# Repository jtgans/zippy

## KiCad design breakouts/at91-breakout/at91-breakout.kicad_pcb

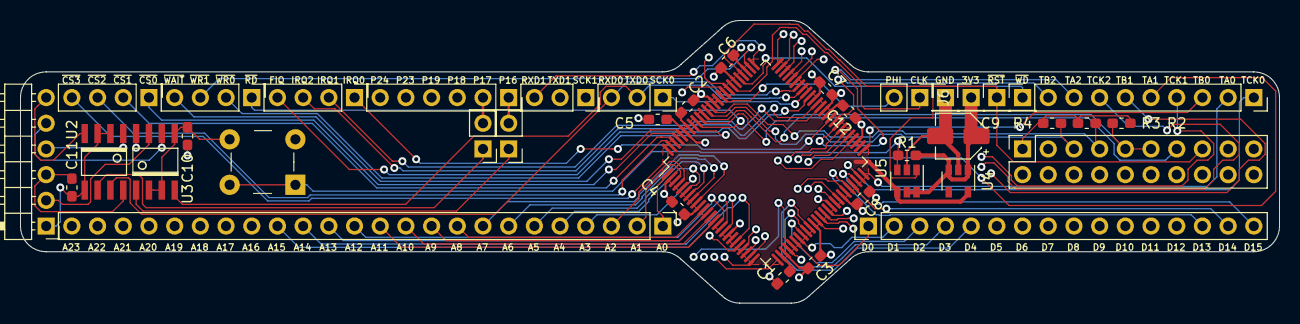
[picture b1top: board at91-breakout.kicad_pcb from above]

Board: 4 copper layers, 124.5 x 27.9 mm, 40 parts (0 on the bottom side), 93 nets.

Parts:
C1, C2, C3, C4, C5, C6, C7, C8, C10, C11, C12: 10nF; C_0603_1608Metric_Pad1.05x0.95mm_HandSolder
C9: 1uF; CP_Elec_4x4.5
J1: UART0; PinSocket_1x03_P2.54mm_Vertical
J2: TIMER; PinSocket_1x09_P2.54mm_Vertical
J3: ADDR[0..23]; PinHeader_1x24_P2.54mm_Vertical
J4: ~WDOVF; PinHeader_1x01_P2.54mm_Vertical
J5: GPIO; PinSocket_1x06_P2.54mm_Vertical
J6: CLKINOUT; PinHeader_1x02_P2.54mm_Vertical
J7: ~RESET; PinHeader_1x01_P2.54mm_Vertical
J8: DATA[0..15]; PinHeader_1x16_P2.54mm_Vertical
J9: ~CS[0..3]; PinHeader_1x04_P2.54mm_Vertical
J10: BUSCTL; PinHeader_1x04_P2.54mm_Vertical
J12: RTSCB0; PinHeader_1x02_P2.54mm_Vertical
J14: IRQ; PinHeader_1x04_P2.54mm_Vertical
J15: JTAG; PinSocket_2x10_P2.54mm_Vertical
J16: CTSCB0; PinHeader_1x02_P2.54mm_Vertical
J18: UART1; PinSocket_1x03_P2.54mm_Vertical
J19: VDD; PinHeader_1x01_P2.54mm_Vertical
J21: GND; PinHeader_1x01_P2.54mm_Vertical
J22: TTY; PinHeader_1x06_P2.54mm_Horizontal
R1, R2, R3, R4: 100K; R_0603_1608Metric_Pad1.05x0.95mm_HandSolder
S1: B3F-1000; Switch_Tactile_THT_B3F-1xxx
U1: AT91R40008; LQFP-100_14x14mm_P0.5mm
U2: BB Powered; SO-8
U3: PC Powered; SO-8
U4: MIC5504-1.8YM5; SOT-23-5
U5: MAX6355TW; SOT-23-6

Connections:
+1V8: C1.2, C2.2, C12.2, U1.27, U1.61, U1.94, U4.5, U5.4
+3V3: C3.2, C4.2, C5.2, C6.2, C7.2, C8.2, C9.1, C10.1, J15.1, J15.2, J19.1, R1.1, R2.1, R3.1, R4.1, U1.10, U1.28, U1.44, U1.62, U1.81, U1.95, U2.8, U4.1, U4.3, U5.5, U5.6
/ADDR0: J3.1, U1.1
/ADDR1: J3.2, U1.3
/ADDR2: J3.3, U1.4
/ADDR3: J3.4, U1.5
/ADDR4: J3.5, U1.6
/ADDR5: J3.6, U1.7
/ADDR6: J3.7, U1.8
/ADDR7: J3.8, U1.9
/ADDR8: J3.9, U1.11
/ADDR9: J3.10, U1.12
/ADDR10: J3.11, U1.13
/ADDR11: J3.12, U1.14
/ADDR12: J3.13, U1.15
/ADDR13: J3.14, U1.16
/ADDR14: J3.15, U1.17
/ADDR15: J3.16, U1.20
/ADDR16: J3.17, U1.21
/ADDR17: J3.18, U1.22
/ADDR18: J3.19, U1.23
/ADDR19: J3.20, U1.24
/ADDR20: J3.21, U1.25
/ADDR21: J3.22, U1.26
/ADDR22: J3.23, U1.29
/ADDR23: J3.24, U1.30
/DATA0: J8.1, U1.31
/DATA1: J8.2, U1.32
/DATA2: J8.3, U1.33
/DATA3: J8.4, U1.34
/DATA4: J8.5, U1.35
/DATA5: J8.6, U1.37
/DATA6: J8.7, U1.38
/DATA7: J8.8, U1.39
/DATA8: J8.9, U1.40
/DATA9: J8.10, U1.41
/DATA10: J8.11, U1.42
/DATA11: J8.12, U1.43
/DATA12: J8.13, U1.45
/DATA13: J8.14, U1.46
/DATA14: J8.15, U1.47
/DATA15: J8.16, U1.48
/FIQ: J14.4, U1.66
/FTDI_GND: C11.2, J22.1, U3.2, U3.3, U3.5
/FTDI_RX: J22.5, U2.6
/FTDI_TX: J22.4, U3.1
/FTDI_VCC: C11.1, J22.3, U3.8
/IRQ0: J14.1, U1.60
/IRQ1: J14.2, U1.63
/IRQ2: J14.3, U1.64
/MCKI: J6.1, U1.82
/MCKO: J6.2, U1.85
/P16: J5.1, J12.2, U1.70
/P17: J5.2, J16.2, U1.71
/P18: J5.3, U1.72
/P19: J5.4, U1.73
/P23: J5.5, U1.83
/P24: J5.6, U1.84
/RXD0: J1.3, U1.69, U3.7
/RXD1: J18.3, U1.76
/SCK0: J1.1, U1.67
/SCK1: J18.1, U1.74
/TCK: J15.9, J15.11, R2.2, U1.91
/TCLK0: J2.1, U1.49
/TCLK1: J2.4, U1.54
/TCLK2: J2.7, U1.57
/TDI: J15.5, R4.2, U1.89
/TDO: J15.13, U1.90
/TIOA0: J2.2, U1.50
/TIOA1: J2.5, U1.55
/TIOA2: J2.8, U1.58
/TIOB0: J2.3, U1.51
/TIOB1: J2.6, U1.56
/TIOB2: J2.9, U1.59
/TMS: J15.7, R3.2, U1.88
/TXD0: J1.2, U1.68, U2.4
/TXD1: J18.2, U1.75
/~CS0: J9.1, U1.97
/~CS1: J9.2, U1.98
/~CS2: J9.3, U1.99
/~CS3: J9.4, U1.100
/~CTS0: J16.1, U3.6
/~FTDI_CTS: J22.2, U2.7
/~FTDI_RTS: J22.6, U3.4
/~MR: R1.2, S1.1, S1.2, U5.3
/~RD: J10.1, U1.92
/~RESET: J7.1, J15.15, U1.79, U5.1
/~RTS0: J12.1, U2.1
/~WAIT: J10.4, U1.96
/~WDOVF: J4.1, U1.80
/~WR0: J10.2, U1.93
/~WR1: J10.3, U1.77
GND: C1.1, C2.1, C3.1, C4.1, C5.1, C6.1, C7.1, C8.1, C9.2, C10.2, C12.1, J15.4, J15.6, J15.8, J15.10, J15.12, J15.14, J15.16, J15.18, J15.20, J21.1, S1.3, S1.4, U1.2, U1.18, U1.19, U1.36, U1.52, U1.53, U1.65, U1.78, U1.86, U1.87, U2.2, U2.3, U2.5, U4.2, U5.2

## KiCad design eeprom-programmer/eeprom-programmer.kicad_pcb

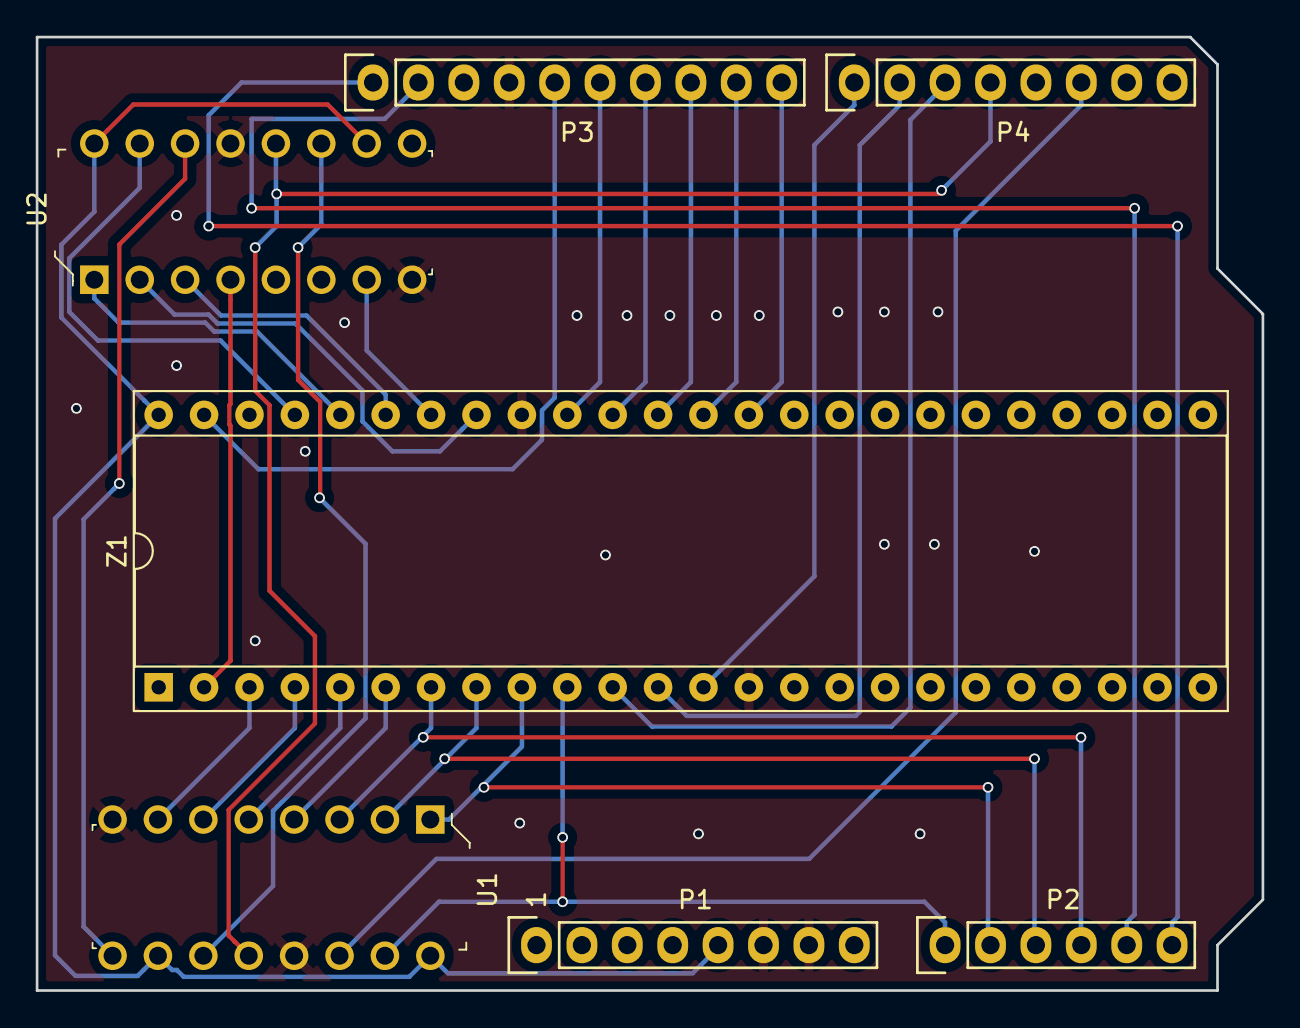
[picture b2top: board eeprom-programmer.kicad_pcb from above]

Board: 2 copper layers, 68.6 x 53.3 mm, 7 parts (0 on the bottom side), 31 nets.

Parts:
P1: Power; Socket_Strip_Arduino_1x08
P2: Analog; Socket_Strip_Arduino_1x06
P3: Digital; Socket_Strip_Arduino_1x10
P4: Digital; Socket_Strip_Arduino_1x08
U1, U2: SN74HC595N; DIP-16_W7.62mm
Z1: 48-6554-11; DIP-48_W15.24mm_Socket

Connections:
+5V: P1.5, U1.10, U1.16, U2.10, U2.16, Z1.48
/2: P4.6, U1.14
/3: U1.11, U2.11
/4: P4.4, U1.12, U2.12
/5(**): P4.3, Z1.11
/6(**): P4.2, Z1.12
/7: P4.1, Z1.13
/8: P3.10, Z1.35
/9(**): P3.9, Z1.36
/10(**/SS): P3.8, Z1.37
/11(**/MOSI): P3.7, Z1.38
/12(MISO): P3.6, Z1.39
/13(SCK): P3.5, Z1.47
/A0: P2.1, U1.15, Z1.10
/A1: P2.2, U1.1, Z1.9
/A2: P2.3, U1.2, Z1.8
/A3: P2.4, U1.3, Z1.7
/A4: U1.4, Z1.6
/A4(SDA): P2.5, P3.2
/A5: U1.5, Z1.5
/A5(SCL): P2.6, P3.1
/A6: U1.6, Z1.4
/A7: U1.7, Z1.3
/A8: U2.15, Z1.45
/A9: U2.1, Z1.44
/A10: U2.2, Z1.41
/A11: U2.3, Z1.43
/A12: U2.4, Z1.2
/~OE: U2.7, Z1.42
GND: P1.6, P1.7, P3.4, U1.8, U1.13, U2.8, U2.13, Z1.14, Z1.40
unnamed: U1.9, U2.14

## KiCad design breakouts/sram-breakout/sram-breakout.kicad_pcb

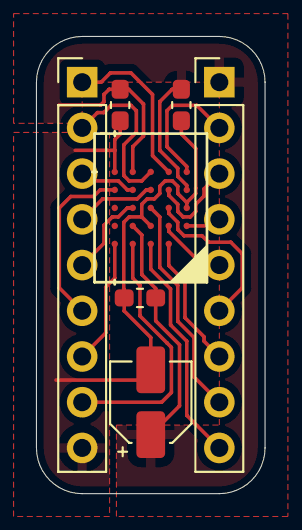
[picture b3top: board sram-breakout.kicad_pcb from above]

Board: 2 copper layers, 12.7 x 25.4 mm, 7 parts (0 on the bottom side), 18 nets.

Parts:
C1, C2, C3: 0.1nF; C_0603_1608Metric_Pad1.05x0.95mm_HandSolder
C4: 0.1uF; CP_Elec_4x4.5
J1, J2: Conn_01x09; PinHeader_1x09_P2.54mm_Vertical
U1: S71KL512SC0

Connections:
+3V3: C1.1, C2.1, C3.1, C4.1, J2.1, U1.B4, U1.D1, U1.E4
/CK: J2.5, U1.B2
/DQ0: J1.4, U1.D3
/DQ1: J2.3, U1.D2
/DQ2: J1.5, U1.C4
/DQ3: J1.3, U1.D4
/DQ4: J1.6, U1.D5
/DQ5: J1.2, U1.E3
/DQ6: J1.1, U1.E2
/DQ7: J2.2, U1.E1
/RWDS: J2.8, U1.C3
/~CK: J2.4, U1.B1
/~CS1: J2.6, U1.C2
/~CS2: J2.9, U1.A3
/~INT: J1.7, U1.A5
/~RESET: J1.8, U1.A4
/~RSTO: J2.7, U1.A2
GND: C1.2, C2.2, C3.2, C4.2, J1.9, U1.B3, U1.C1, U1.E5

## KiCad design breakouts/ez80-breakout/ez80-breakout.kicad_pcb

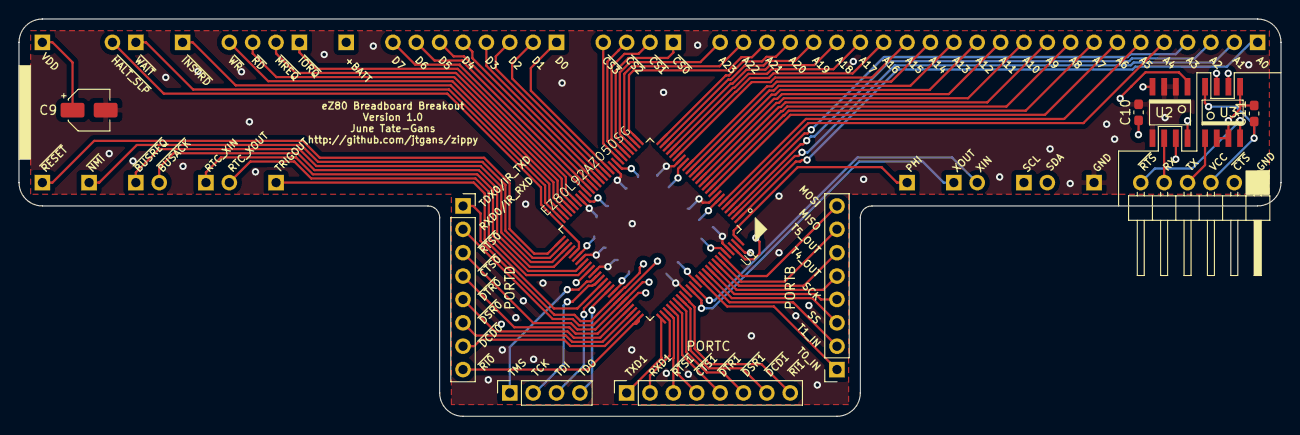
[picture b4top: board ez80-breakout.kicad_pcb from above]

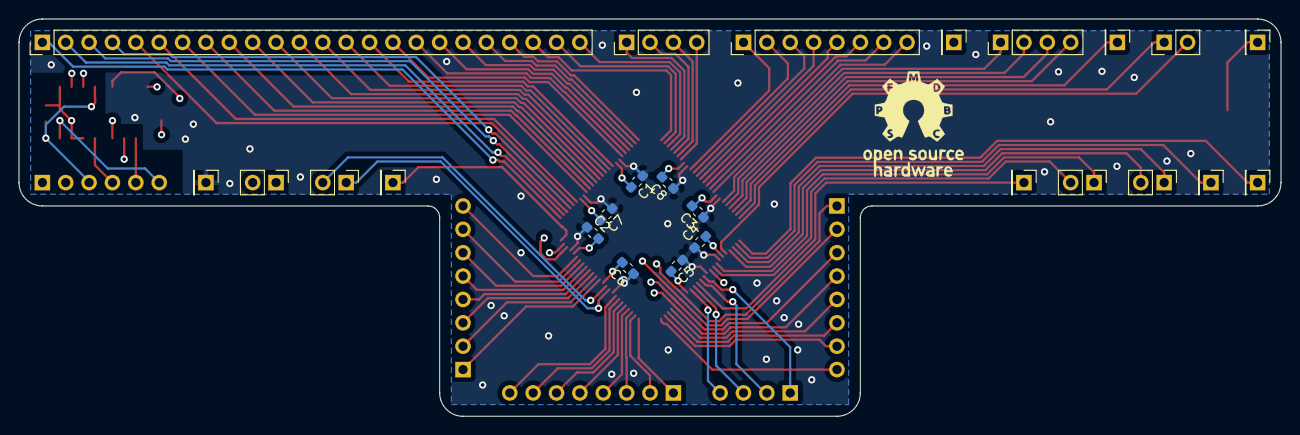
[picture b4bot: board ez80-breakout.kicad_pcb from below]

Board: 4 copper layers, 137.2 x 43.2 mm, 36 parts (25 on the bottom side), 92 nets.

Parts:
C1, C2, C3, C4, C5, C6, C7, C8, C10, C11: 10nF; C_0603_1608Metric_Pad1.05x0.95mm_HandSolder
C9: 1uF; CP_Elec_4x4.5
J1: PORTD; PinSocket_1x08_P2.54mm_Vertical
J2: PORTC; PinSocket_1x08_P2.54mm_Vertical
J3: ADDR[0..23]; PinHeader_1x24_P2.54mm_Vertical
J4: I2C; PinHeader_1x02_P2.54mm_Vertical
J5: RTC_XINOUT; PinHeader_1x02_P2.54mm_Vertical
J6: XINOUT; PinHeader_1x02_P2.54mm_Vertical
J7: ~RESET; PinHeader_1x01_P2.54mm_Vertical
J8: DATA[0..7]; PinHeader_1x08_P2.54mm_Vertical
J9: ~CS[0..3]; PinHeader_1x04_P2.54mm_Vertical
J10: IRQ & Mem; PinHeader_1x04_P2.54mm_Vertical
J11: ~INSTRD; PinHeader_1x01_P2.54mm_Vertical
J12: ~WAIT; PinHeader_1x02_P2.54mm_Vertical
J13: ~BUSREQACK; PinHeader_1x02_P2.54mm_Vertical
J14: ~NMI; PinHeader_1x01_P2.54mm_Vertical
J15: ZDI; PinSocket_1x04_P2.54mm_Vertical
J16: TRIGOUT; PinHeader_1x01_P2.54mm_Vertical
J17: PHI; PinHeader_1x01_P2.54mm_Vertical
J18: PORTB; PinSocket_1x08_P2.54mm_Vertical
J19: VDD; PinHeader_1x01_P2.54mm_Vertical
J20: RTC_VDD; PinHeader_1x01_P2.54mm_Vertical
J21: GND; PinHeader_1x01_P2.54mm_Vertical
J22: TTY; PinHeader_1x06_P2.54mm_Horizontal
U1: EZ80L92AZ050SG; QFP50P1600X1600X160-100N
U2: BB Powered; SO-8
U3: PC Powered; SO-8

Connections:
+3V3: C1.2, C2.2, C3.2, C4.2, C5.2, C6.2, C7.2, C8.2, C9.1, C10.1, J19.1, U1.7, U1.18, U1.33, U1.43, U1.56, U1.67, U1.87, U1.96, U2.8
+BATT: J20.1, U1.60
/ADDR0: J3.1, U1.1
/ADDR1: J3.2, U1.2
/ADDR2: J3.3, U1.3
/ADDR3: J3.4, U1.4
/ADDR4: J3.5, U1.5
/ADDR5: J3.6, U1.6
/ADDR6: J3.7, U1.9
/ADDR7: J3.8, U1.10
/ADDR8: J3.9, U1.11
/ADDR9: J3.10, U1.12
/ADDR10: J3.11, U1.13
/ADDR11: J3.12, U1.14
/ADDR12: J3.13, U1.15
/ADDR13: J3.14, U1.16
/ADDR14: J3.15, U1.17
/ADDR15: J3.16, U1.20
/ADDR16: J3.17, U1.21
/ADDR17: J3.18, U1.22
/ADDR18: J3.19, U1.23
/ADDR19: J3.20, U1.24
/ADDR20: J3.21, U1.25
/ADDR21: J3.22, U1.26
/ADDR22: J3.23, U1.27
/ADDR23: J3.24, U1.28
/DATA0: J8.1, U1.35
/DATA1: J8.2, U1.36
/DATA2: J8.3, U1.37
/DATA3: J8.4, U1.38
/DATA4: J8.5, U1.39
/DATA5: J8.6, U1.40
/DATA6: J8.7, U1.41
/DATA7: J8.8, U1.42
/FTDI_GND: C11.2, J22.1, U3.2, U3.3, U3.5
/FTDI_RX: J22.5, U2.6
/FTDI_TX: J22.4, U3.1
/FTDI_VCC: C11.1, J22.3, U3.8
/PB0: J18.1, U1.88
/PB1: J18.2, U1.89
/PB2: J18.3, U1.90
/PB3: J18.4, U1.91
/PB4: J18.5, U1.92
/PB5: J18.6, U1.93
/PB6: J18.7, U1.94
/PB7: J18.8, U1.95
/PC0: J2.1, U1.76
/PC1: J2.2, U1.77
/PC2: J2.3, U1.78
/PC3: J2.4, U1.79
/PC4: J2.5, U1.80
/PC5: J2.6, U1.81
/PC6: J2.7, U1.82
/PC7: J2.8, U1.83
/PD0: J1.1, U1.68, U2.4
/PD1: J1.2, U1.69, U3.7
/PD2: J1.3, U1.70, U2.1
/PD3: J1.4, U1.71, U3.6
/PD4: J1.5, U1.72
/PD5: J1.6, U1.73
/PD6: J1.7, U1.74
/PD7: J1.8, U1.75
/PHI: J17.1, U1.100
/RTC_XIN: J5.1, U1.58
/RTC_XOUT: J5.2, U1.59
/SCL: J4.1, U1.99
/SDA: J4.2, U1.98
/TCK: J15.2, U1.63
/TDI: J15.3, U1.65
/TDO: J15.4, U1.66
/TMS: J15.1, U1.62
/TRIGOUT: J16.1, U1.64
/XIN: J6.1, U1.85
/XOUT: J6.2, U1.86
/~BUSACK: J13.2, U1.54
/~BUSREQ: J13.1, U1.53
/~CS0: J9.1, U1.29
/~CS1: J9.2, U1.30
/~CS2: J9.3, U1.31
/~CS3: J9.4, U1.32
/~FTDI_CTS: J22.2, U2.7
/~FTDI_RTS: J22.6, U3.4
/~HALT_SLP: J12.2, U1.55
/~INSTRD: J11.1, U1.49
/~IORQ: J10.1, U1.45
/~MREQ: J10.2, U1.46
/~NMI: J14.1, U1.52
/~RD: J10.3, U1.47
/~RESET: J7.1, U1.51
/~WAIT: J12.1, U1.50
/~WR: J10.4, U1.48
GND: C1.1, C2.1, C3.1, C4.1, C5.1, C6.1, C7.1, C8.1, C9.2, C10.2, J21.1, U1.8, U1.19, U1.34, U1.44, U1.57, U1.61, U1.84, U1.97, U2.2, U2.3, U2.5

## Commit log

2019-09-16 Initial commit of the Zippy project.
2019-09-16 Adding in the ignore file.
2019-09-16 Removing ignored files.
2019-09-16 Removing the accidental rescue library.
2019-09-18 Committing the basics.
2019-09-18 Import of the major redesign and most of the schematic.
2019-09-20 Crowbar updates and ERC fixes
    This updates the Crowbar bus connectors and the layout of the
    schematic to match the finalized pinouts. It also corrects an
    error in the original schematic where the buses were not
    properly routing due to lack of labels.
    Finally, this change includes fixes for the ERC and adds the CPU
    and RTC crystals to the system.
2019-09-21 System management, serial I/O, and power refinement
    - Swapped the XTAL for the CPU to the programmable OSC.
    - Cleaned up the decoupling caps according to datasheets
    and "rule of thumb" experimental results in
    https://www.edn.com/design/components-and-packaging/4351231/EDN-Access-09-01-95-Don-t-let-rules-of-thumb-set-decoupling-capacitor-value
    - Added an ATMega328 for use as a system management uC.
    Primarily used for soft power on/off of the ATX PSU
2019-09-21 Import the digikey kicad library and add it to the project.
2019-09-21 Cleanups and pruning
    - Migrated the Crowbar backplane out to the top level and
    promoted most of the signals to hierarchical labels.
    - Added a sheet for memory. Just a placeholder for now.
    - Wired up all the rest of the signals properly.
2019-09-21 Addition of the main bus pins to the memory sheet.
2019-10-12 Bookmark of where I'm at in the layout.
    Last step for the serial debug interface is to route the RX/TX
    lines through the opto-isolators and then to the eZ80 and the
    supervisor uC.
2019-10-13 symbols: Update USBGND to be a Zippy-specific symbol
    I accidentally made this in the eeschema power library, which
    is totally wrong.
2019-10-13 debug: First draft of opto-isolation
    This is the first pass of integrating opto isolators into the
    debug conectors for the board.
2019-10-13 crowbar: Reworking the pinout again
    - Completely reworked the pinout of the crowbar bus to match the
    spec.
    - Added lines for eZ80 -> SMC I2C
    - Added lines for SMC -> Crowbar I2C
    - Migrated Crowbar power pinouts to their own sub-sheet
2019-10-13 toplevel: Add in SPI_SSx, IRQx, and INSTRD
    - Create the SPI_SSx and IRQx pins in the CPU schematic
    - Create the INSTRD pin in the memory schematic
    - Wire things up on the toplevel
2019-10-14 crowbar: Wire in INTx and SPI_SSx
    This wires in the INTx lines into the B port, with the SPI_SSx
    lines tied into the upper bits of the B port as well.
2019-10-15 memory: Add in three 32Mb SRAM chips
    This is the initial version of the 32Mb SRAM symbols and initial
    placement in the memory subsheet. Things to do still:
    - Import the the PLA chip symbol and wire it up
    - Import the EEPROM Boot ROM chip symbol and wire it up
    - Wire in power and decoupling chips
2019-11-01 Major rework of the system RAM integration - Wired up the jellybean logic for the RAM chip selects. - Reorganized various bits here and there. - Added preliminary symbols for the jellybean logic.
2019-11-02 gitignore: Add more files we don't care about.
2019-11-02 boot rom: Add in the symbol for the Flash and integrate into the system - Add the Flash ROM schematic symbol. - Add to the ram-rom schematic. - Get rid of /INSTRD -- not really useful. - Export /CS0 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
2019-11-03 zippy: Migrate all fo the zippy stuff into its own subdir
2019-11-03 breakout: Create an eZ80 breadboard breakout board
2019-11-04 ez80 breakout: Create a breadboard compatible eZ80 Breakout
    Additionally:
    - Import the OSHW logo
    - Draw up SO-8 footprint for the opto-isolators
2019-11-04 ez80 breakout: Add courtyard for the whole board
2019-11-04 ez80 breakout: Add PWR_FLAGs
2019-11-05 ez80 breakout: Thicken outer Edge.Cuts line to workaround OSHPark problem
2019-12-27 Importing sram breakout
2019-12-27 Updating schematics to the latest kicad
2019-12-27 Swap to relative paths.
2019-12-28 Import some bringup programs
2019-12-28 Add in the hello-world UART program
2019-12-28 Laid out the HyperRAM PSRAM breakout PCB
2019-12-28 Add in some notes for the next rev of the ez80 breakout.
2019-12-29 Updating SRAM breakout board to be 0.3 inch wide
2019-12-29 Fixing the ez80-breakout symbol tables.
2019-12-29 Adding AT91R40008 breakout board and symbol
2019-12-29 blinky: Fix the jp conditional, adjust RAM version for ADL mode
2019-12-29 Add a small program to scribble over memory regions.
2019-12-29 Don't commit binary artifacts.
2019-12-30 Importing the Arduino EEPROM programmer shield schematic.
2019-12-31 Finished routing the AT91 breakout board
    May want to reroute later. It wasn't the best job.
2020-01-01 Adding silkscreen labels for pins on AT91 breakout board.
